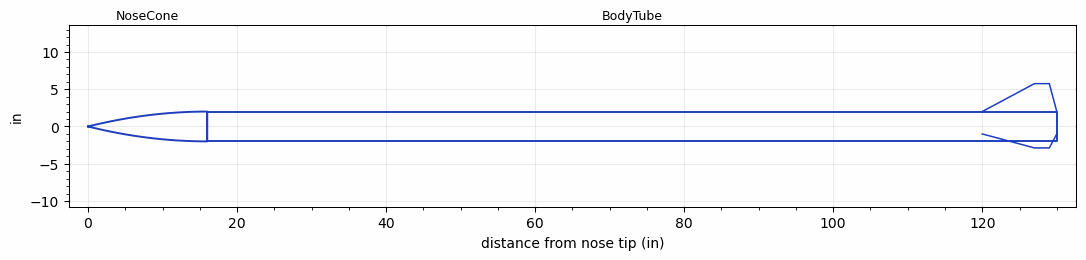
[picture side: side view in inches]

<RASAeroDocument>
 <FileVersion>2</FileVersion>
 <RocketDesign>
  <NoseCone>
   <Length>16</Length>
   <Diameter>4</Diameter>
   <Shape>Parabolic</Shape>
   <Location>0</Location>
  </NoseCone>
  <BodyTube>
   <Length>114</Length>
   <Diameter>4</Diameter>
   <Location>16</Location>
   <Fin>
    <Count>3</Count>
    <Chord>10</Chord>
    <Span>3.75</Span>
    <SweepDistance>7</SweepDistance>
    <TipChord>2</TipChord>
    <Thickness>0.25</Thickness>
    <LERadius>0.125</LERadius>
    <Location>10</Location>
    <AirfoilSection>Double Wedge</AirfoilSection>
    <FX1>1</FX1>
   </Fin>
  </BodyTube>
  <Surface>Camouflage Paint</Surface>
  <ModifiedBarrowman>False</ModifiedBarrowman>
  <Turbulence>False</Turbulence>
  <UseBooster1>False</UseBooster1>
  <UseBooster2>False</UseBooster2>
 </RocketDesign>
 <LaunchSite>
  <Altitude>5000</Altitude>
  <Pressure>0</Pressure>
  <RodAngle>7</RodAngle>
  <RodLength>4</RodLength>
  <Temperature>95</Temperature>
  <WindSpeed>8</WindSpeed>
 </LaunchSite>
 <Recovery>
  <Altitude1>1000</Altitude1>
  <Altitude2>1000</Altitude2>
  <DeviceType1>None</DeviceType1>
  <DeviceType2>None</DeviceType2>
  <Event1>False</Event1>
  <Event2>False</Event2>
  <Size1>1</Size1>
  <Size2>1</Size2>
  <EventType1>None</EventType1>
  <EventType2>None</EventType2>
  <CD1>1.33</CD1>
  <CD2>1.33</CD2>
 </Recovery>
 <SimulationList>
  <Simulation>
   <SustainerEngine>L1350-CS-P  (CTI)</SustainerEngine>
   <SustainerLaunchWt>36</SustainerLaunchWt>
   <SustainerNozzleDiameter>1</SustainerNozzleDiameter>
   <SustainerCG>60</SustainerCG>
   <SustainerIgnitionDelay>0</SustainerIgnitionDelay>
   <Booster1SeparationDelay>0</Booster1SeparationDelay>
   <Booster1IgnitionDelay>0</Booster1IgnitionDelay>
   <IncludeBooster1>False</IncludeBooster1>
   <Booster2Delay>0</Booster2Delay>
   <IncludeBooster2>False</IncludeBooster2>
   <TimetoApogee>23.45044</TimetoApogee>
   <MaxAltitude>8511.987</MaxAltitude>
   <MaxVelocity>798.4844</MaxVelocity>
  </Simulation>
  <Simulation>
   <SustainerEngine>M1560-WT  (CTI)</SustainerEngine>
   <SustainerLaunchWt>39</SustainerLaunchWt>
   <SustainerCG>65</SustainerCG>
   <SustainerIgnitionDelay>0</SustainerIgnitionDelay>
   <Booster1SeparationDelay>0</Booster1SeparationDelay>
   <Booster1IgnitionDelay>0</Booster1IgnitionDelay>
   <IncludeBooster1>False</IncludeBooster1>
   <Booster2Delay>0</Booster2Delay>
   <IncludeBooster2>False</IncludeBooster2>
   <TimetoApogee>26.2205</TimetoApogee>
   <MaxAltitude>10803.1</MaxAltitude>
   <MaxVelocity>924.9676</MaxVelocity>
  </Simulation>
  <Simulation>
   <SustainerEngine>M1810-RL  (CTI)</SustainerEngine>
   <SustainerLaunchWt>40</SustainerLaunchWt>
   <SustainerCG>64.5</SustainerCG>
   <SustainerIgnitionDelay>0</SustainerIgnitionDelay>
   <Booster1SeparationDelay>0</Booster1SeparationDelay>
   <Booster1IgnitionDelay>0</Booster1IgnitionDelay>
   <IncludeBooster1>False</IncludeBooster1>
   <Booster2Delay>0</Booster2Delay>
   <IncludeBooster2>False</IncludeBooster2>
   <TimetoApogee>28.61056</TimetoApogee>
   <MaxAltitude>13318.07</MaxAltitude>
   <MaxVelocity>1068.097</MaxVelocity>
  </Simulation>
  <Simulation>
   <SustainerEngine>M1230-IM  (CTI)</SustainerEngine>
   <SustainerLaunchWt>39</SustainerLaunchWt>
   <SustainerCG>64</SustainerCG>
   <SustainerIgnitionDelay>0</SustainerIgnitionDelay>
   <Booster1SeparationDelay>0</Booster1SeparationDelay>
   <Booster1IgnitionDelay>0</Booster1IgnitionDelay>
   <IncludeBooster1>False</IncludeBooster1>
   <Booster2Delay>0</Booster2Delay>
   <IncludeBooster2>False</IncludeBooster2>
   <TimetoApogee>27.13053</TimetoApogee>
   <MaxAltitude>11304.14</MaxAltitude>
   <MaxVelocity>920.8649</MaxVelocity>
  </Simulation>
  <Simulation>
   <SustainerEngine>L3200-VM-P  (CTI)</SustainerEngine>
   <SustainerLaunchWt>35</SustainerLaunchWt>
   <SustainerCG>59</SustainerCG>
   <SustainerIgnitionDelay>0</SustainerIgnitionDelay>
   <Booster1SeparationDelay>0</Booster1SeparationDelay>
   <Booster1IgnitionDelay>0</Booster1IgnitionDelay>
   <IncludeBooster1>False</IncludeBooster1>
   <Booster2Delay>0</Booster2Delay>
   <IncludeBooster2>False</IncludeBooster2>
   <TimetoApogee>19.15034</TimetoApogee>
   <MaxAltitude>5999.208</MaxAltitude>
   <MaxVelocity>681.2643</MaxVelocity>
  </Simulation>
 </SimulationList>
</RASAeroDocument>
